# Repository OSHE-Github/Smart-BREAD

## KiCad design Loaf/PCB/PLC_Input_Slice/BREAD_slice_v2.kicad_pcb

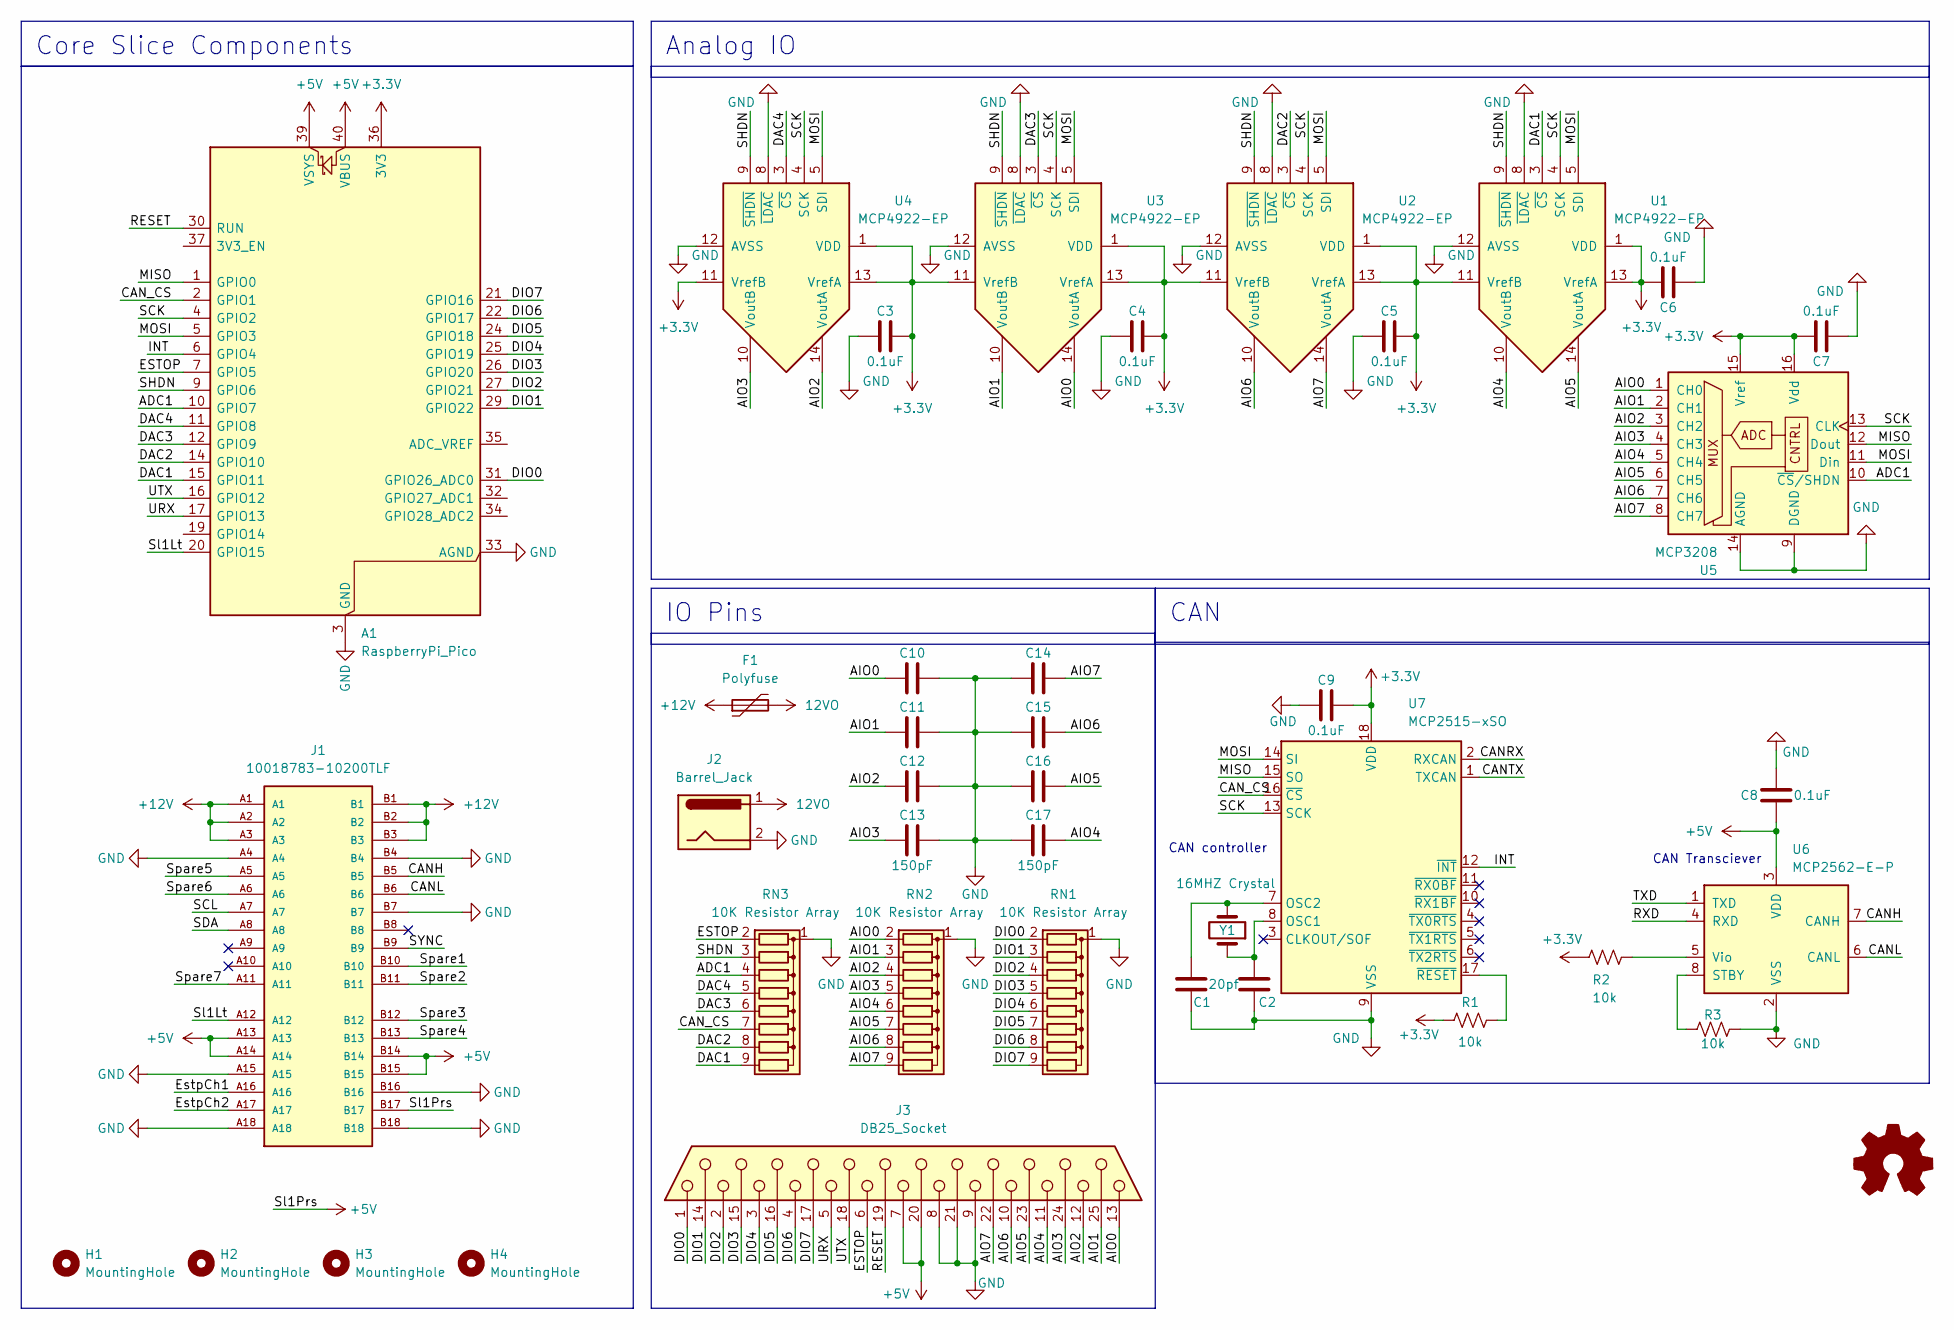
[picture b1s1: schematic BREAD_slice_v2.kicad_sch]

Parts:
A1: RaspberryPi_Pico; RaspberryPi_Pico_Common_Unspecified
C1, C2: 20pf; C_1206_3216Metric_Pad1.33x1.80mm_HandSolder
C3, C4, C5, C6, C7, C8, C9: 0.1uF; C_1206_3216Metric_Pad1.33x1.80mm_HandSolder
C10, C11, C12, C13, C14, C15, C16, C17: 150pF; C_1206_3216Metric_Pad1.33x1.80mm_HandSolder
F1: Polyfuse; Fuse_2920_7451Metric_Pad2.10x5.45mm_HandSolder
H1, H2, H3, H4: MountingHole; MountingHole_3.2mm_M3_DIN965_Pad
J1: 10018783-10200TLF; BUS_PCIexpress_x1; PARTREV Z
J2: Barrel_Jack; BarrelJack_CUI_PJ-063AH_Horizontal
J3: DB25_Socket; DSUB-25_Socket_Horizontal_P2.77x2.84mm_EdgePinOffset4.94mm_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
Logo1: Logo_Open_Hardware_Small; OSHW-Symbol_6.7x6mm_SilkScreen
R1, R2, R3: 10k; R_1206_3216Metric_Pad1.30x1.75mm_HandSolder
RN1, RN2, RN3: 10K Resistor Array; R_Array_SIP9
U1, U2, U3, U4: MCP4922-EP; DIP-14_W7.62mm
U5: MCP3208; DIP-16_W7.62mm_LongPads
U6: MCP2562-E-P; DIP-8_W7.62mm
U7: MCP2515-xSO; DIP-18_W7.62mm
Y1: 16MHZ Crystal; Crystal_HC49-4H_Vertical

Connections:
12VO: F1.2, J2.1
+3.3V: A1.36 (3V3), C3.2, C4.2, C5.2, C6.2, C7.2, C9.2, R1.2, R2.1, U1.1 (VDD), U1.11 (VrefB), U1.13 (VrefA), U2.1 (VDD), U2.11 (VrefB), U2.13 (VrefA), U3.1 (VDD), U3.11 (VrefB), U3.13 (VrefA), U4.1 (VDD), U4.11 (VrefB), U4.13 (VrefA), U5.15 (Vref), U5.16 (Vdd), U7.18 (VDD)
+5V: A1.39 (VSYS), A1.40 (VBUS), C8.2, J1.A13, J1.A14, J1.B14, J1.B15, J1.B17, J3.7, J3.20, U6.3 (VDD)
+12V: F1.1, J1.A1, J1.A2, J1.A3, J1.B1, J1.B2, J1.B3
/ADC1: A1.10 (GPIO7), RN3.4 (R3), U5.10 (~CS/SHDN)
/AIO0: C10.1, J3.13, RN2.2 (R1), U3.14 (VoutA), U5.1 (CH0)
/AIO1: C11.1, J3.25, RN2.3 (R2), U3.10 (VoutB), U5.2 (CH1)
/AIO2: C12.1, J3.12, RN2.4 (R3), U4.14 (VoutA), U5.3 (CH2)
/AIO3: C13.1, J3.24, RN2.5 (R4), U4.10 (VoutB), U5.4 (CH3)
/AIO4: C17.2, J3.11, RN2.6 (R5), U1.10 (VoutB), U5.5 (CH4)
/AIO5: C16.2, J3.23, RN2.7 (R6), U1.14 (VoutA), U5.6 (CH5)
/AIO6: C15.2, J3.10, RN2.8 (R7), U2.10 (VoutB), U5.7 (CH6)
/AIO7: C14.2, J3.22, RN2.9 (R8), U2.14 (VoutA), U5.8 (CH7)
/CANH: J1.B5, U6.7 (CANH)
/CANL: J1.B6, U6.6 (CANL)
/CANRX: U7.2 (RXCAN)
/CANTX: U7.1 (TXCAN)
/CAN_CS: A1.2 (GPIO1), RN3.7 (R6), U7.16 (~CS)
/DAC1: A1.15 (GPIO11), RN3.9 (R8), U1.3 (~CS)
/DAC2: A1.14 (GPIO10), RN3.8 (R7), U2.3 (~CS)
/DAC3: A1.12 (GPIO9), RN3.6 (R5), U3.3 (~CS)
/DAC4: A1.11 (GPIO8), RN3.5 (R4), U4.3 (~CS)
/DIO0: A1.31 (GPIO26_ADC0), J3.1, RN1.2 (R1)
/DIO1: A1.29 (GPIO22), J3.14, RN1.3 (R2)
/DIO2: A1.27 (GPIO21), J3.2, RN1.4 (R3)
/DIO3: A1.26 (GPIO20), J3.15, RN1.5 (R4)
/DIO4: A1.25 (GPIO19), J3.3, RN1.6 (R5)
/DIO5: A1.24 (GPIO18), J3.16, RN1.7 (R6)
/DIO6: A1.22 (GPIO17), J3.4, RN1.8 (R7)
/DIO7: A1.21 (GPIO16), J3.17, RN1.9 (R8)
/ESTOP: A1.7 (GPIO5), J3.6, RN3.2 (R1)
/EstpCh1: J1.A16
/EstpCh2: J1.A17
/INT: A1.6 (GPIO4), U7.12 (~INT)
/MISO: A1.1 (GPIO0), U5.12 (Dout), U7.15 (SO)
/MOSI: A1.5 (GPIO3), U1.5 (SDI), U2.5 (SDI), U3.5 (SDI), U4.5 (SDI), U5.11 (Din), U7.14 (SI)
/RESET: A1.30 (RUN), J3.19
/RXD: U6.4 (RXD)
/SCK: A1.4 (GPIO2), U1.4 (SCK), U2.4 (SCK), U3.4 (SCK), U4.4 (SCK), U5.13 (CLK), U7.13 (SCK)
/SCL: J1.A7
/SDA: J1.A8
/SHDN: A1.9 (GPIO6), RN3.3 (R2), U1.9 (~SHDN), U2.9 (~SHDN), U3.9 (~SHDN), U4.9 (~SHDN)
/SYNC: J1.B9
/Sl1Lt: A1.20 (GPIO15), J1.A12
/Spare1: J1.B10
/Spare2: J1.B11
/Spare3: J1.B12
/Spare4: J1.B13
/Spare5: J1.A5
/Spare6: J1.A6
/Spare7: J1.A11
/TXD: U6.1 (TXD)
/URX: A1.17 (GPIO13), J3.5
/UTX: A1.16 (GPIO12), J3.18
GND: A1.3 (GND), A1.8 (GND), A1.13 (GND), A1.18 (GND), A1.23 (GND), A1.28 (GND), A1.33 (AGND), A1.38 (GND), C1.2, C2.2, C3.1, C4.1, C5.1, C6.1, C7.1, C8.1, C9.1, C10.2, C11.2, C12.2, C13.2, C14.1, C15.1, C16.1, C17.1, J1.A4, J1.A15, J1.A18, J1.B4, J1.B7, J1.B16, J1.B18, J2.2, J3.8, J3.9, J3.21, R3.1, RN1.1 (common), RN2.1 (common), RN3.1 (common), U1.8 (~LDAC), U1.12 (AVSS), U2.8 (~LDAC), U2.12 (AVSS), U3.8 (~LDAC), U3.12 (AVSS), U4.8 (~LDAC), U4.12 (AVSS), U5.9 (DGND), U5.14 (AGND), U6.2 (VSS), U7.9 (VSS)
unnamed: R3.2, U6.8 (STBY)
unnamed: R2.2, U6.5 (Vio)
unnamed: C2.1, U7.8 (OSC1), Y1.1
unnamed: C1.1, U7.7 (OSC2), Y1.2
unnamed: R1.1, U7.17 (~RESET)

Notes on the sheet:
CAN Transciever
CAN controller
CAN
IO Pins
Analog IO
Core Slice Components

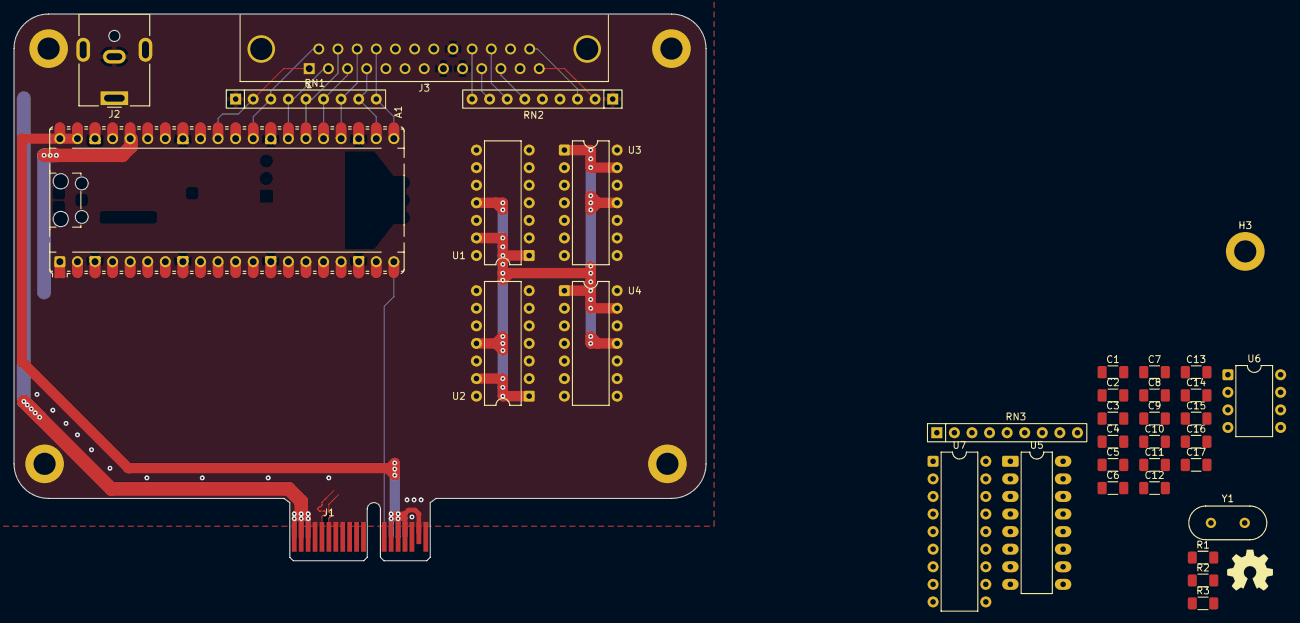
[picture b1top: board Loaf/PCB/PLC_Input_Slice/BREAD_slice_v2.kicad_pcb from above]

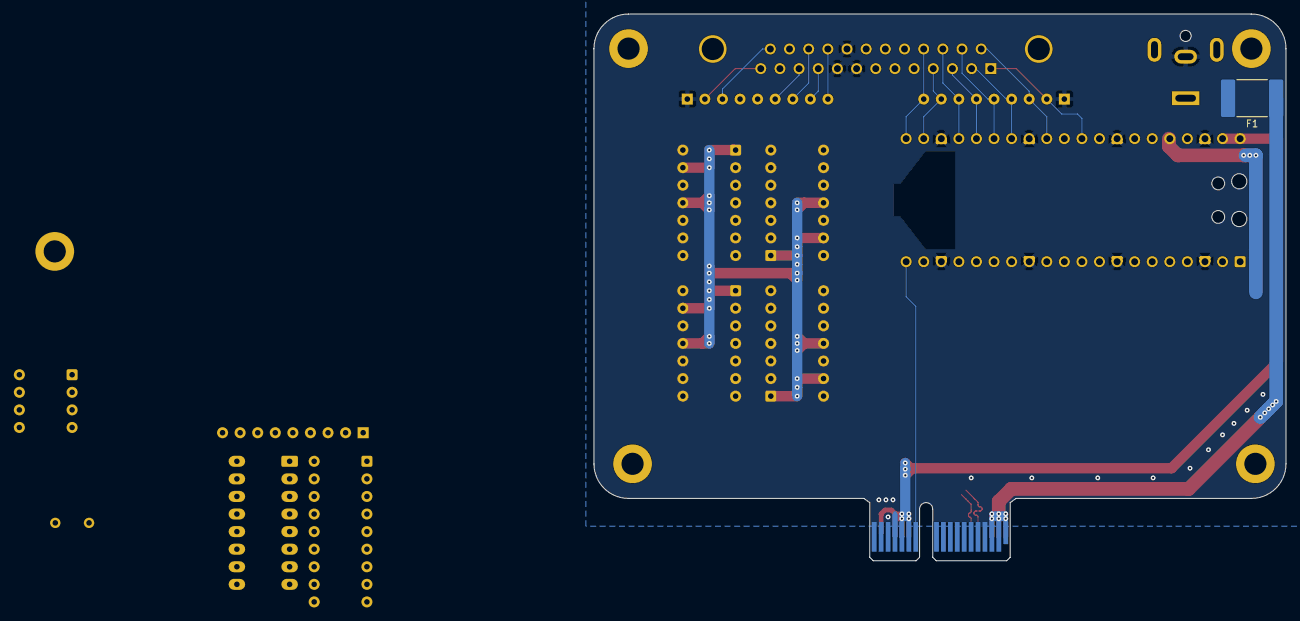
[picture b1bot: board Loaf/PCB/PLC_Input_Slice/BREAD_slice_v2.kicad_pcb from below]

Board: 2 copper layers, 100.0 x 79.0 mm, 42 parts (5 on the bottom side), 44 nets.

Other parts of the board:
H1#2: MountingHole; MountingHole_3.2mm_M3_DIN965_Pad

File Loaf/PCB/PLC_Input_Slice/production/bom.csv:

Designator,Footprint,Quantity,Value,LCSC Part #
A1,RaspberryPi_Pico_Common_Unspecified,1,RaspberryPi_Pico,
"C1, C2",1206,2,20pf,
"C10, C11, C12, C13, C14, C15, C16, C17",1206,8,150pF,
"C3, C4, C5, C6, C7, C8, C9",1206,7,0.1uF,
F1,2920,1,Polyfuse,
J1,BUS_PCIexpress_x1,1,10018783-10200TLF,
J2,BarrelJack_CUI_PJ-063AH_Horizontal,1,Barrel_Jack,
J3,DSUB-25_Socket_Horizontal_P2.77x2.84mm_EdgePinOffset4.94mm_Housed_MountingHolesOffset4.94mm,1,DB25_Socket,
LOGO1,OSHW-Symbol_6.7x6mm_SilkScreen,1,Logo_Open_Hardware_Small,
"R1, R2",1206,2,10k,
"RN1, RN2, RN3",R_Array_SIP9,3,10K Resistor Array,
"U1, U2, U3, U4",DIP-14_W7.62mm,4,MCP4922-EP,
U5,DIP-16_W7.62mm_LongPads,1,MCP3208,
U6,DIP-8_W7.62mm,1,MCP2561-E-P,
U7,DIP-18_W7.62mm,1,MCP2515-xSO,
Y1,Crystal_HC49-4H_Vertical,1,16MHZ Crystal,

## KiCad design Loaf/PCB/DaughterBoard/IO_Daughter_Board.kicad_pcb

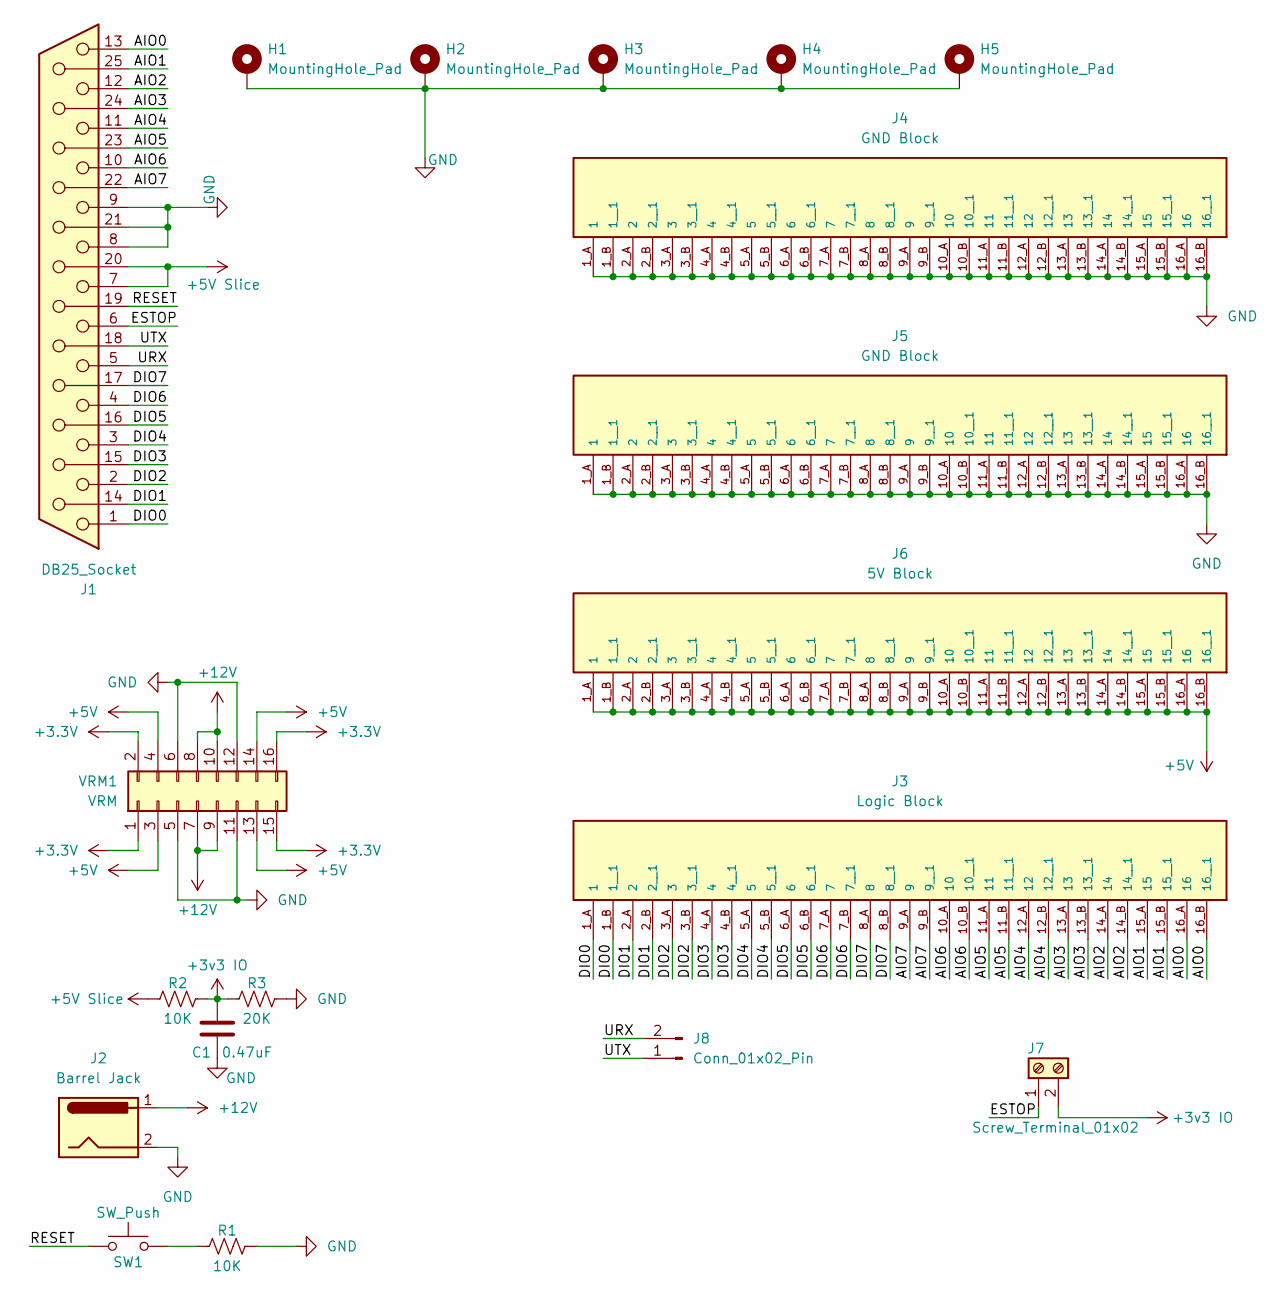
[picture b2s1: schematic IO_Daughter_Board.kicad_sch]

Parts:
C1: 0.47uF; C_1206_3216Metric_Pad1.33x1.80mm_HandSolder
H1, H2, H3, H4, H5: MountingHole_Pad; MountingHole_3.2mm_M3_DIN965_Pad
J1: DB25_Socket; DSUB-25_Socket_Horizontal_P2.77x2.84mm_EdgePinOffset4.94mm_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
J2: Barrel Jack; BarrelJack_CUI_PJ-063AH_Horizontal
J3: Logic Block; CUI_TBL009-254-16GY-2GY
J4, J5: GND Block; CUI_TBL009-254-16GY-2GY
J6: 5V Block; CUI_TBL009-254-16GY-2GY
J7: Screw_Terminal_01x02; TerminalBlock_MaiXu_MX126-5.0-02P_1x02_P5.00mm
J8: Conn_01x02_Pin; PinHeader_1x02_P2.54mm_Horizontal
R1, R2: 10K; R_1206_3216Metric_Pad1.30x1.75mm_HandSolder
R3: 20K; R_1206_3216Metric_Pad1.30x1.75mm_HandSolder
SW1: SW_Push; SW_Tactile_Straight_KSL0Axx1LFTR
VRM1: VRM; PinSocket_2x08_P2.54mm_Vertical

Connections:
+3.3V: VRM1.1, VRM1.2, VRM1.15, VRM1.16
+3v3 IO: C1.2, J7.2, R2.2, R3.1
+5V: J6.1_A (1), J6.1_B (1__1), J6.2_A (2), J6.2_B (2__1), J6.3_A (3), J6.3_B (3__1), J6.4_A (4), J6.4_B (4__1), J6.5_A (5), J6.5_B (5__1), J6.6_A (6), J6.6_B (6__1), J6.7_A (7), J6.7_B (7__1), J6.8_A (8), J6.8_B (8__1), J6.9_A (9), J6.9_B (9__1), J6.10_A (10), J6.10_B (10__1), J6.11_A (11), J6.11_B (11__1), J6.12_A (12), J6.12_B (12__1), J6.13_A (13), J6.13_B (13__1), J6.14_A (14), J6.14_B (14__1), J6.15_A (15), J6.15_B (15__1), J6.16_A (16), J6.16_B (16__1), VRM1.3, VRM1.4, VRM1.13, VRM1.14
+5V Slice: J1.7, J1.20, R2.1
+12V: J2.1, VRM1.7, VRM1.8, VRM1.9, VRM1.10
/AIO0: J1.13, J3.16_A (16), J3.16_B (16__1)
/AIO1: J1.25, J3.15_A (15), J3.15_B (15__1)
/AIO2: J1.12, J3.14_A (14), J3.14_B (14__1)
/AIO3: J1.24, J3.13_A (13), J3.13_B (13__1)
/AIO4: J1.11, J3.12_A (12), J3.12_B (12__1)
/AIO5: J1.23, J3.11_A (11), J3.11_B (11__1)
/AIO6: J1.10, J3.10_A (10), J3.10_B (10__1)
/AIO7: J1.22, J3.9_A (9), J3.9_B (9__1)
/DIO0: J1.1, J3.1_A (1), J3.1_B (1__1)
/DIO1: J1.14, J3.2_A (2), J3.2_B (2__1)
/DIO2: J1.2, J3.3_A (3), J3.3_B (3__1)
/DIO3: J1.15, J3.4_A (4), J3.4_B (4__1)
/DIO4: J1.3, J3.5_A (5), J3.5_B (5__1)
/DIO5: J1.16, J3.6_A (6), J3.6_B (6__1)
/DIO6: J1.4, J3.7_A (7), J3.7_B (7__1)
/DIO7: J1.17, J3.8_A (8), J3.8_B (8__1)
/ESTOP: J1.6, J7.1
/RESET: J1.19, SW1.1
/URX: J1.5, J8.2
/UTX: J1.18, J8.1
GND: C1.1, H1.1 (1_1), H2.1 (1_1), H3.1 (1_1), H4.1 (1_1), H5.1 (1_1), J1.8, J1.9, J1.21, J2.2, J4.1_A (1), J4.1_B (1__1), J4.2_A (2), J4.2_B (2__1), J4.3_A (3), J4.3_B (3__1), J4.4_A (4), J4.4_B (4__1), J4.5_A (5), J4.5_B (5__1), J4.6_A (6), J4.6_B (6__1), J4.7_A (7), J4.7_B (7__1), J4.8_A (8), J4.8_B (8__1), J4.9_A (9), J4.9_B (9__1), J4.10_A (10), J4.10_B (10__1), J4.11_A (11), J4.11_B (11__1), J4.12_A (12), J4.12_B (12__1), J4.13_A (13), J4.13_B (13__1), J4.14_A (14), J4.14_B (14__1), J4.15_A (15), J4.15_B (15__1), J4.16_A (16), J4.16_B (16__1), J5.1_A (1), J5.1_B (1__1), J5.2_A (2), J5.2_B (2__1), J5.3_A (3), J5.3_B (3__1), J5.4_A (4), J5.4_B (4__1), J5.5_A (5), J5.5_B (5__1), J5.6_A (6), J5.6_B (6__1), J5.7_A (7), J5.7_B (7__1), J5.8_A (8), J5.8_B (8__1), J5.9_A (9), J5.9_B (9__1), J5.10_A (10), J5.10_B (10__1), J5.11_A (11), J5.11_B (11__1), J5.12_A (12), J5.12_B (12__1), J5.13_A (13), J5.13_B (13__1), J5.14_A (14), J5.14_B (14__1), J5.15_A (15), J5.15_B (15__1), J5.16_A (16), J5.16_B (16__1), R1.2, R3.2, VRM1.5, VRM1.6, VRM1.11, VRM1.12
unnamed: R1.1, SW1.2

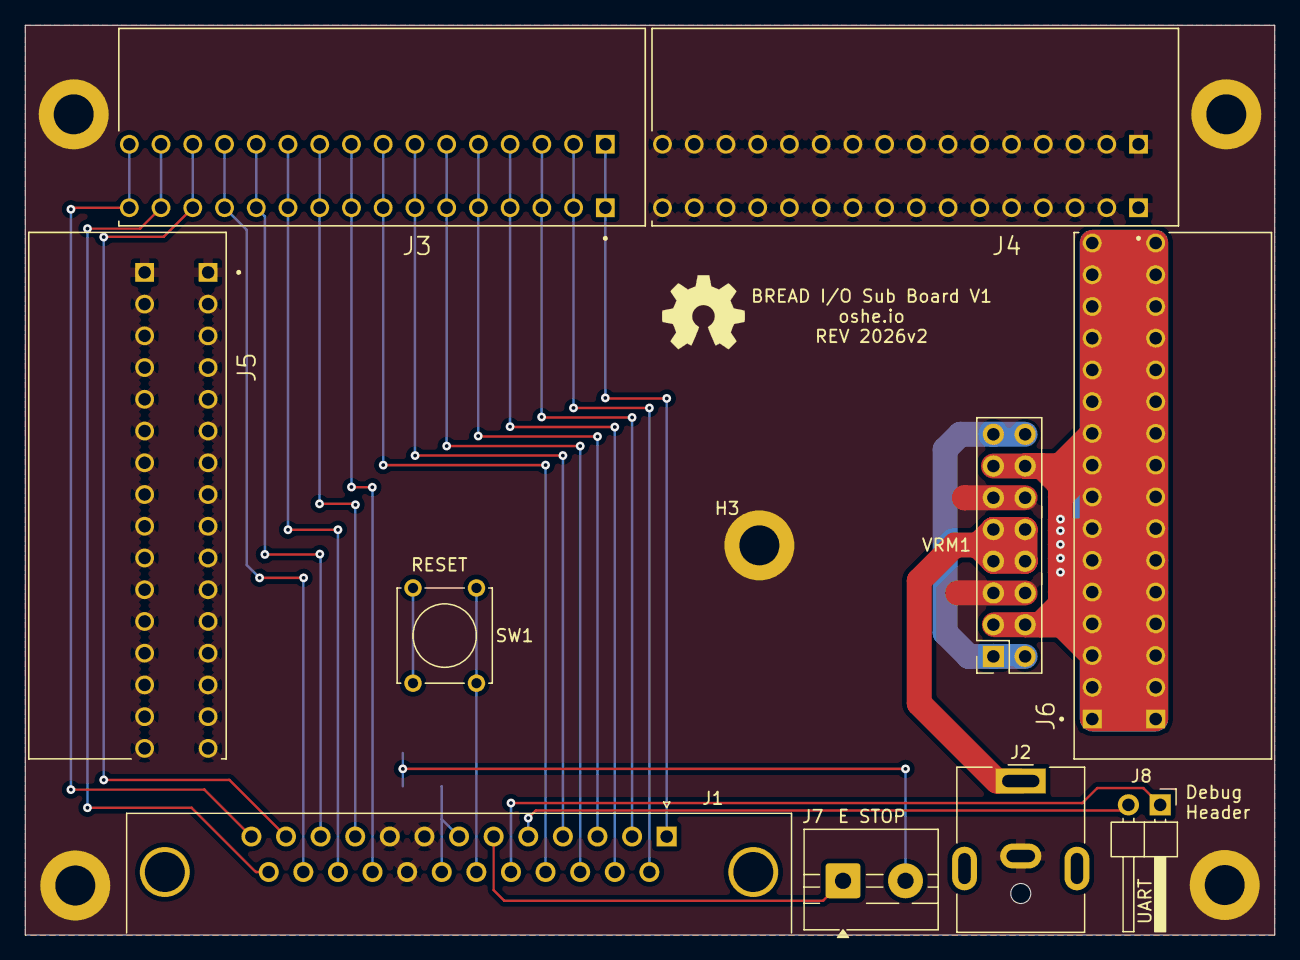
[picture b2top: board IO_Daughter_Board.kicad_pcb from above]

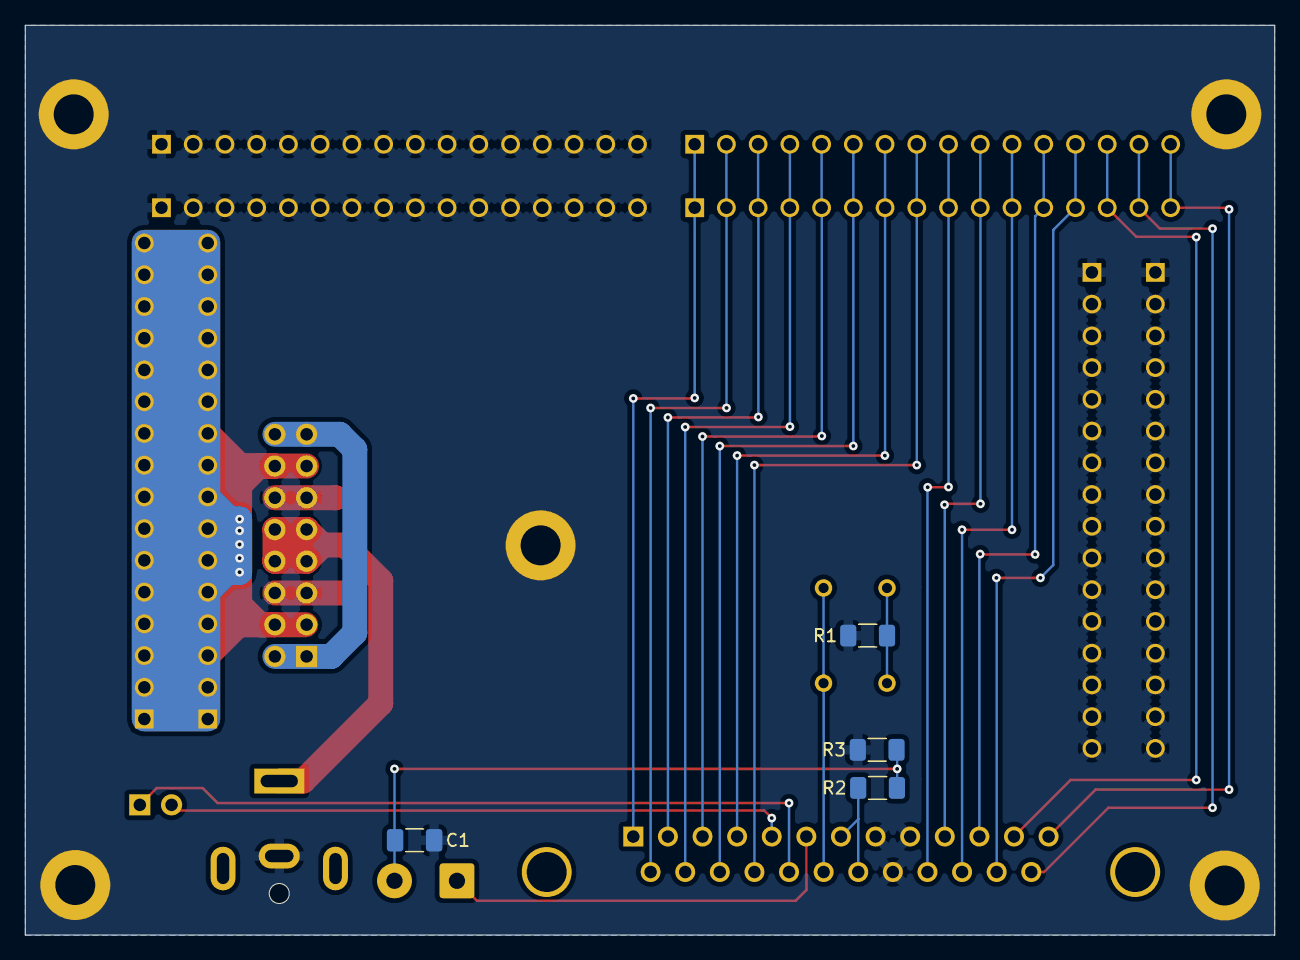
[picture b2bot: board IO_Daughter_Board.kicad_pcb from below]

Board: 2 copper layers, 100.0 x 72.8 mm, 20 parts (4 on the bottom side), 27 nets.

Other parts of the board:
Logo1: Logo_Open_Hardware_Small; OSHW-Symbol_6.7x6mm_SilkScreen

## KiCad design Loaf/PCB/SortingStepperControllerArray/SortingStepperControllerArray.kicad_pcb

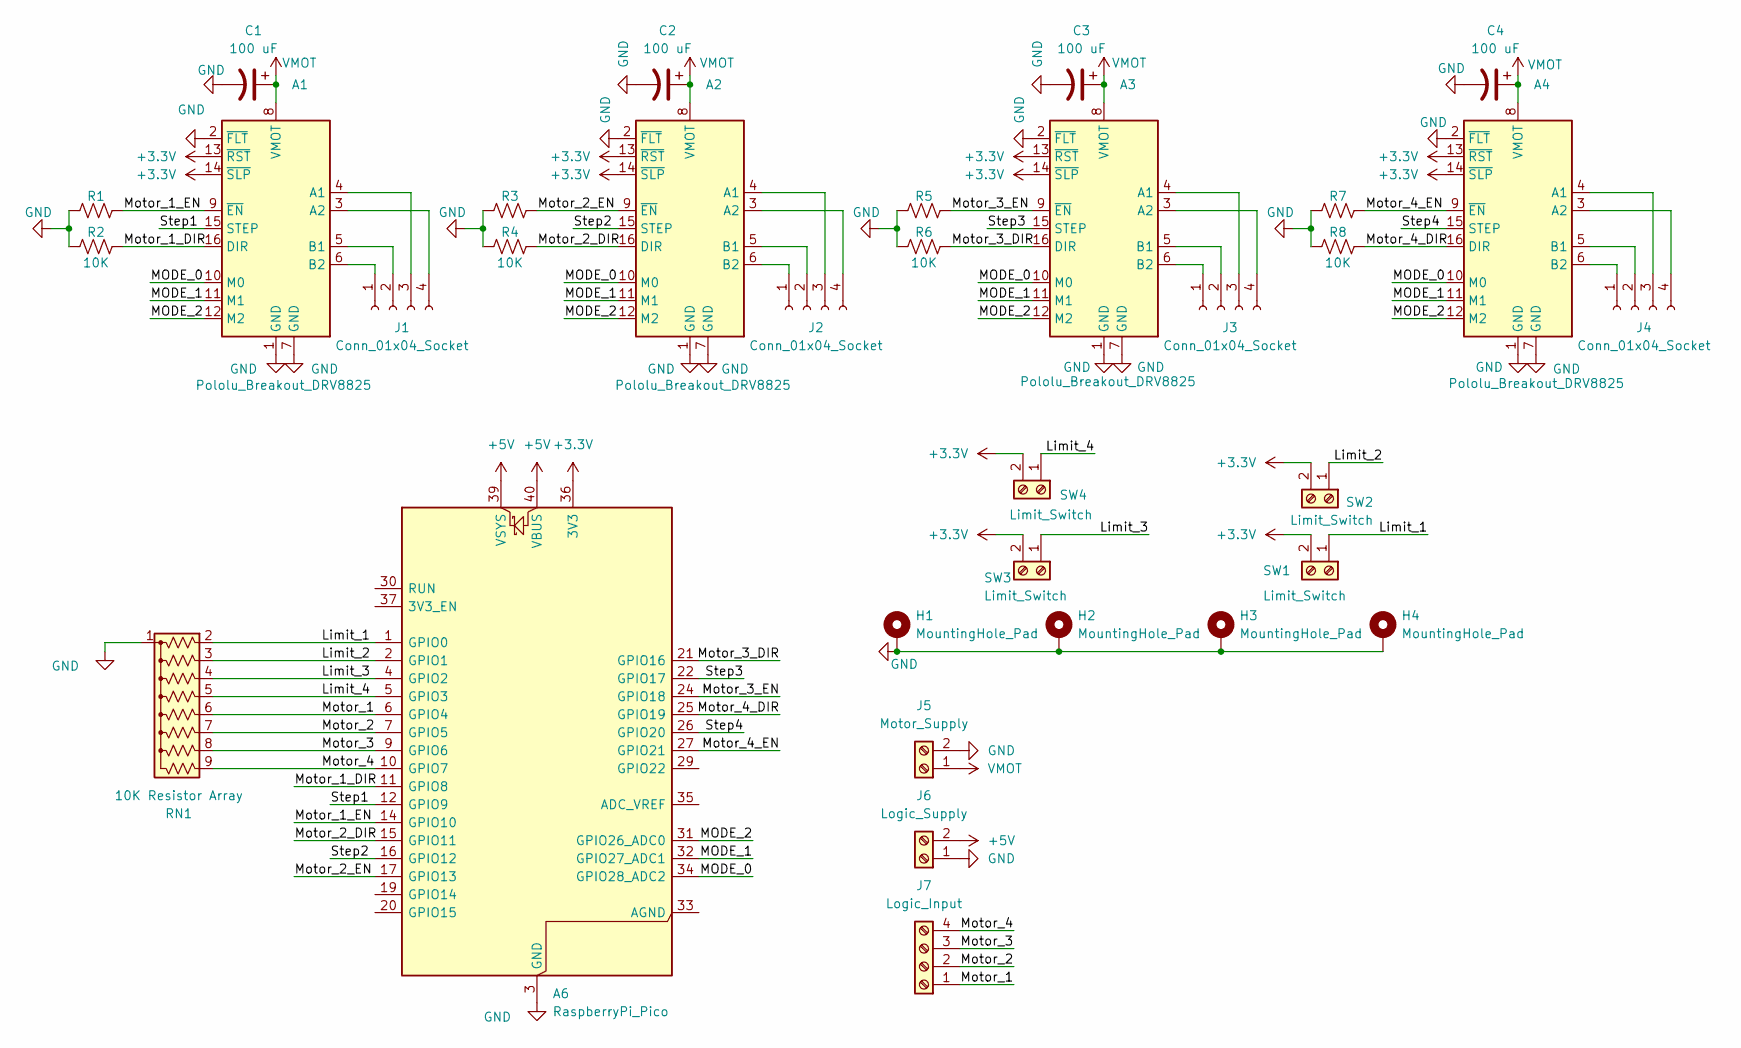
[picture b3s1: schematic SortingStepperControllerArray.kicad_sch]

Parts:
A1, A2, A3, A4: Pololu_Breakout_DRV8825; Pololu_Breakout-16_15.2x20.3mm
A6: RaspberryPi_Pico; RaspberryPi_Pico_Common_Unspecified
C1, C2, C3, C4: 100 uF; CP_Radial_D8.0mm_P3.50mm
H1, H2, H3, H4: MountingHole_Pad; MountingHole_3.2mm_M3_DIN965_Pad
J1, J2, J3, J4: Conn_01x04_Socket; JST_XH_B4B-XH-A_1x04_P2.50mm_Vertical
J5: Motor_Supply; TerminalBlock_TE_282834-2_1x02_P2.54mm_Horizontal
J6: Logic_Supply; TerminalBlock_TE_282834-2_1x02_P2.54mm_Horizontal
J7: Logic_Input; TerminalBlock_TE_282834-4_1x04_P2.54mm_Horizontal
R1, R2, R3, R4, R5, R6, R7, R8: 10K; R_1206_3216Metric_Pad1.30x1.75mm_HandSolder
RN1: 10K Resistor Array; R_Array_SIP9
SW1, SW2, SW3, SW4: Limit_Switch; TerminalBlock_TE_282834-2_1x02_P2.54mm_Horizontal

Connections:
+3.3V: A1.13 (~RST), A1.14 (~SLP), A2.13 (~RST), A2.14 (~SLP), A3.13 (~RST), A3.14 (~SLP), A4.13 (~RST), A4.14 (~SLP), A6.36 (3V3), SW1.2, SW2.2, SW3.2, SW4.2
+5V: A6.39 (VSYS), A6.40 (VBUS), J6.2
/Limit_1: A6.1 (GPIO0), RN1.2 (R1), SW1.1
/Limit_2: A6.2 (GPIO1), RN1.3 (R2), SW2.1
/Limit_3: A6.4 (GPIO2), RN1.4 (R3), SW3.1
/Limit_4: A6.5 (GPIO3), RN1.5 (R4), SW4.1
/MODE_0: A1.10 (M0), A2.10 (M0), A3.10 (M0), A4.10 (M0), A6.34 (GPIO28_ADC2)
/MODE_1: A1.11 (M1), A2.11 (M1), A3.11 (M1), A4.11 (M1), A6.32 (GPIO27_ADC1)
/MODE_2: A1.12 (M2), A2.12 (M2), A3.12 (M2), A4.12 (M2), A6.31 (GPIO26_ADC0)
/Motor_1: A6.6 (GPIO4), J7.1, RN1.6 (R5)
/Motor_1_DIR: A1.16 (DIR), A6.11 (GPIO8), R2.2
/Motor_1_EN: A1.9 (~EN), A6.14 (GPIO10), R1.2
/Motor_2: A6.7 (GPIO5), J7.2, RN1.7 (R6)
/Motor_2_DIR: A2.16 (DIR), A6.15 (GPIO11), R4.2
/Motor_2_EN: A2.9 (~EN), A6.17 (GPIO13), R3.2
/Motor_3: A6.9 (GPIO6), J7.3, RN1.8 (R7)
/Motor_3_DIR: A3.16 (DIR), A6.21 (GPIO16), R6.2
/Motor_3_EN: A3.9 (~EN), A6.24 (GPIO18), R5.2
/Motor_4: A6.10 (GPIO7), J7.4, RN1.9 (R8)
/Motor_4_DIR: A4.16 (DIR), A6.25 (GPIO19), R8.2
/Motor_4_EN: A4.9 (~EN), A6.27 (GPIO21), R7.2
/Step1: A1.15 (STEP), A6.12 (GPIO9)
/Step2: A2.15 (STEP), A6.16 (GPIO12)
/Step3: A3.15 (STEP), A6.22 (GPIO17)
/Step4: A4.15 (STEP), A6.26 (GPIO20)
GND: A1.1 (GND), A1.2 (~FLT), A1.7 (GND), A2.1 (GND), A2.2 (~FLT), A2.7 (GND), A3.1 (GND), A3.2 (~FLT), A3.7 (GND), A4.1 (GND), A4.2 (~FLT), A4.7 (GND), A6.3 (GND), A6.8 (GND), A6.13 (GND), A6.18 (GND), A6.23 (GND), A6.28 (GND), A6.38 (GND), C1.2, C2.2, C3.2, C4.2, H1.1 (1_1), H2.1 (1_1), H3.1 (1_1), H4.1 (1_1), J5.2, J6.1, R1.1, R2.1, R3.1, R4.1, R5.1, R6.1, R7.1, R8.1, RN1.1 (common)
unnamed: A1.4 (A1), J1.3
unnamed: A1.3 (A2), J1.4
unnamed: A1.5 (B1), J1.2
unnamed: A1.6 (B2), J1.1
unnamed: A2.4 (A1), J2.3
unnamed: A2.3 (A2), J2.4
unnamed: A2.5 (B1), J2.2
unnamed: A2.6 (B2), J2.1
unnamed: A3.4 (A1), J3.3
unnamed: A3.3 (A2), J3.4
unnamed: A3.5 (B1), J3.2
unnamed: A3.6 (B2), J3.1
unnamed: A4.4 (A1), J4.3
unnamed: A4.3 (A2), J4.4
unnamed: A4.5 (B1), J4.2
unnamed: A4.6 (B2), J4.1
VMOT: A1.8 (VMOT), A2.8 (VMOT), A3.8 (VMOT), A4.8 (VMOT), C1.1, C2.1, C3.1, C4.1, J5.1

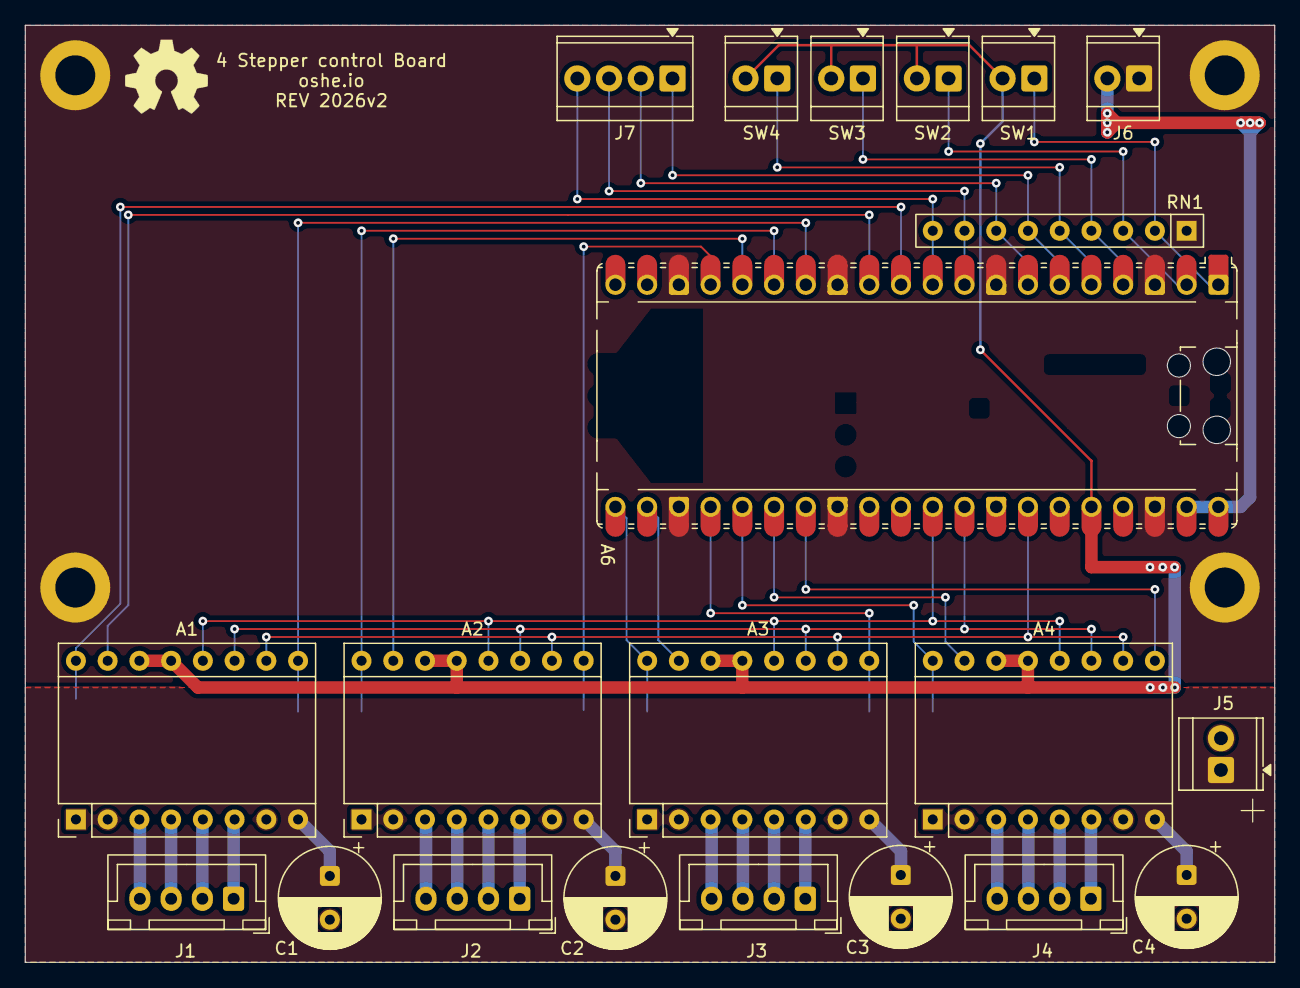
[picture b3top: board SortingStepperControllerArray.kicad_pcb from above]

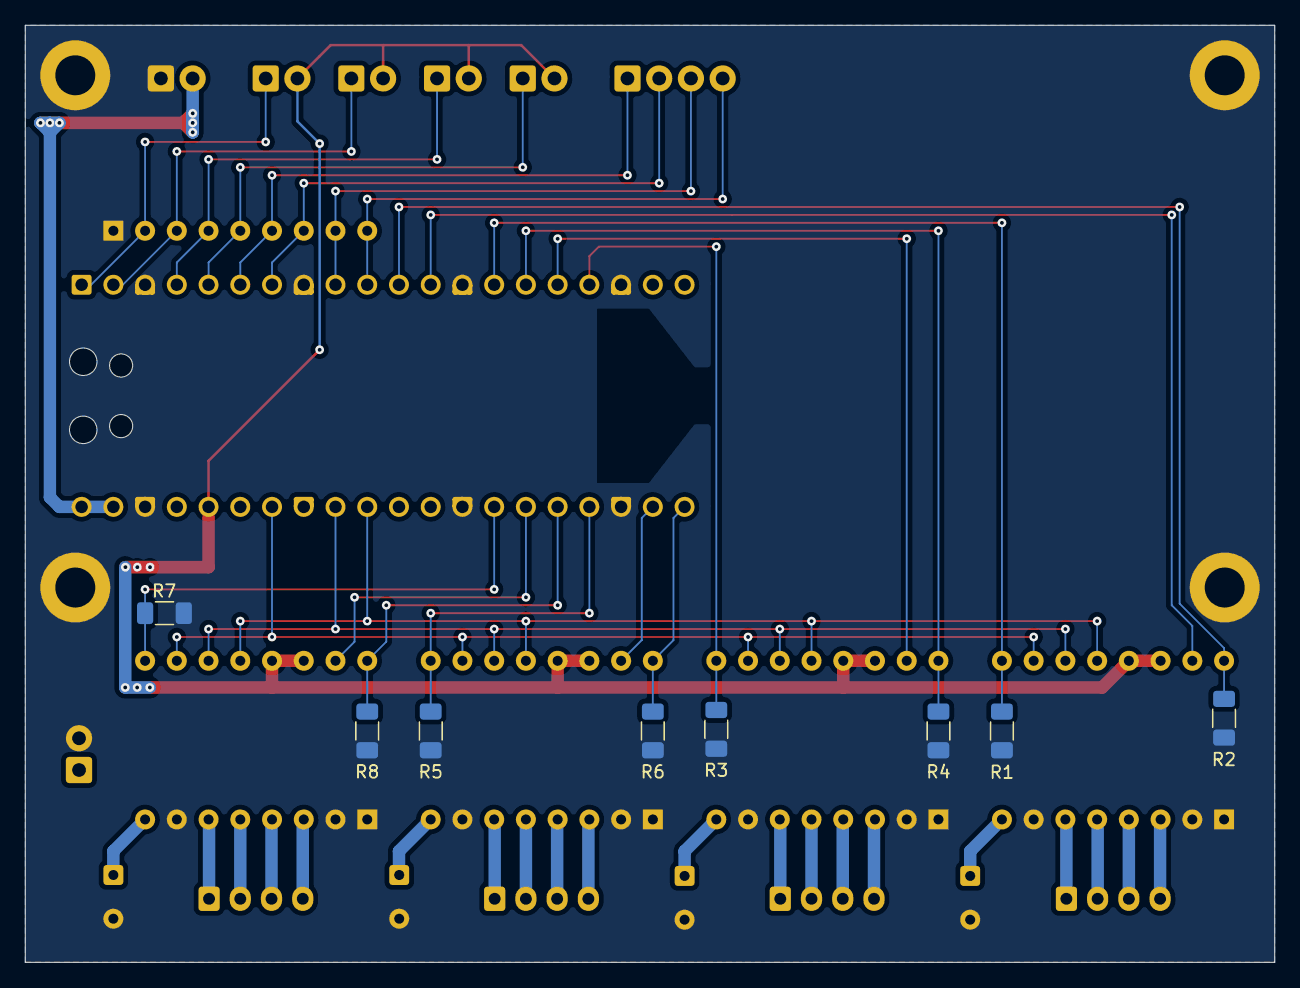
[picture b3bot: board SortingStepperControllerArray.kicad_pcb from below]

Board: 2 copper layers, 100.0 x 75.0 mm, 34 parts (8 on the bottom side), 43 nets.

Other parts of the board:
Logo1: Logo_Open_Hardware_Small; OSHW-Symbol_6.7x6mm_SilkScreen

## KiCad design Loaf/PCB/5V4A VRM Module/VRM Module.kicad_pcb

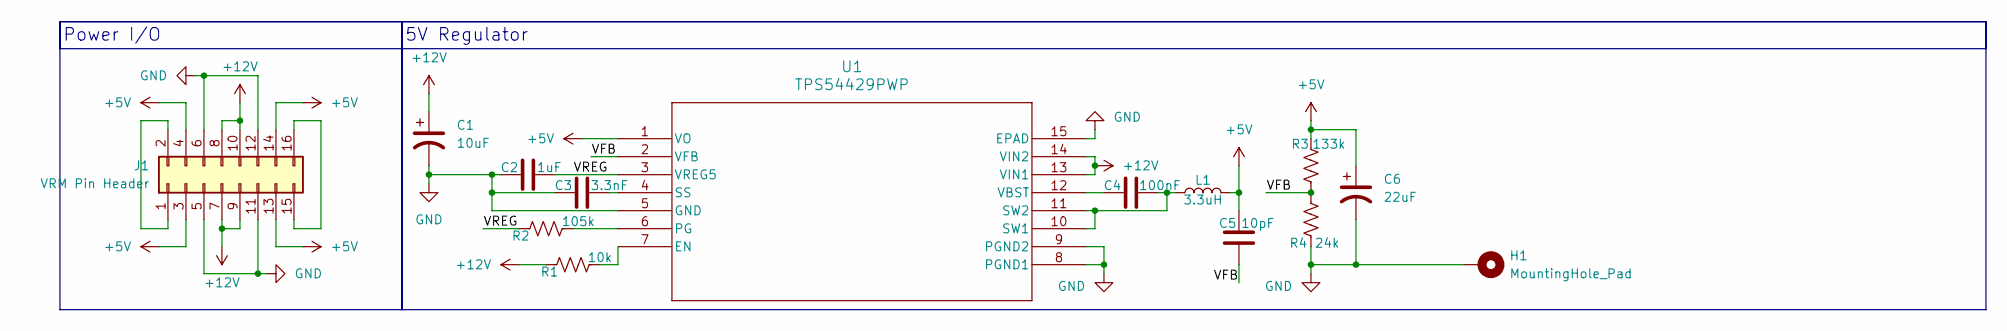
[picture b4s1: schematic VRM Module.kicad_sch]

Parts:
C1: 10uF; CP_Radial_D5.0mm_P2.50mm
C2: 1uF; C_1206_3216Metric_Pad1.33x1.80mm_HandSolder
C3: 3.3nF; C_1206_3216Metric_Pad1.33x1.80mm_HandSolder
C4: 100nF; C_1206_3216Metric_Pad1.33x1.80mm_HandSolder
C5: 10pF; C_1206_3216Metric_Pad1.33x1.80mm_HandSolder
C6: 22uF; CP_Radial_D5.0mm_P2.50mm
H1: MountingHole_Pad; MountingHole_3.2mm_M3_DIN965_Pad
J1: VRM Pin Header; PinHeader_2x08_P2.54mm_Vertical
L1: 3.3uH; R_1206_3216Metric_Pad1.30x1.75mm_HandSolder
R1: 10k; R_1206_3216Metric_Pad1.30x1.75mm_HandSolder
R2: 105k; R_1206_3216Metric_Pad1.30x1.75mm_HandSolder
R3: 133k; R_1206_3216Metric_Pad1.30x1.75mm_HandSolder
R4: 24k; R_1206_3216Metric_Pad1.30x1.75mm_HandSolder
U1: TPS54429PWP; Texas_HTSSOP-14-1EP_4.4x5mm_P0.65mm_EP3.4x5mm_Mask2.94x3.34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

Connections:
+5V: C5.2, C6.1, J1.3, J1.4, J1.13, J1.14, L1.2, R3.2, U1.1 (VO)
+12V: C1.1, J1.7, J1.8, J1.9, J1.10, R1.1, U1.13 (VIN1), U1.14 (VIN2)
/VFB: C5.1, R3.1, R4.2, U1.2 (VFB)
/VREG: C2.2, R2.1, U1.3 (VREG5)
GND: C1.2, C2.1, C3.1, C6.2, H1.1 (1_1), J1.5, J1.6, J1.11, J1.12, R4.1, U1.5 (GND), U1.8 (PGND1), U1.9 (PGND2), U1.15 (EPAD)
unnamed: J1.1, J1.2
unnamed: J1.15, J1.16
unnamed: R1.2, U1.7 (EN)
unnamed: R2.2, U1.6 (PG)
unnamed: C3.2, U1.4 (SS)
unnamed: C4.2, L1.1, U1.10 (SW1), U1.11 (SW2)
unnamed: C4.1, U1.12 (VBST)

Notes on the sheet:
5V Regulator
Power I/O

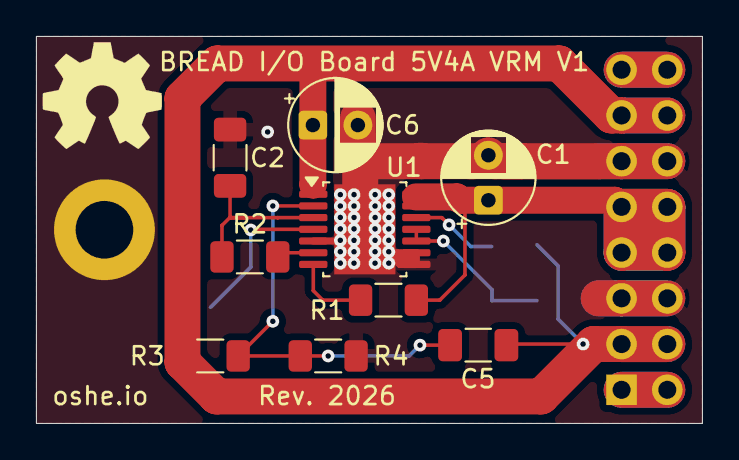
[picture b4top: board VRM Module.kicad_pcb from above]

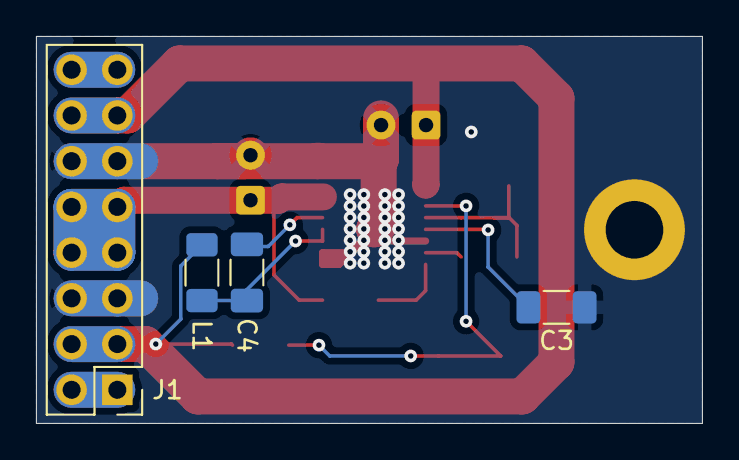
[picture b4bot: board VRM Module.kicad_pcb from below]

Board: 2 copper layers, 37.0 x 21.5 mm, 15 parts (5 on the bottom side), 12 nets.

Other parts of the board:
Logo1: Logo_Open_Hardware_Small; OSHW-Symbol_6.7x6mm_SilkScreen

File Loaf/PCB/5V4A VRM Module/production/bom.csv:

Designator,Footprint,Quantity,Value,LCSC Part #
C1,CP_Radial_D5.0mm_P2.50mm,1,10uF,
C2,1206,1,1uF,
C3,1206,1,3.3uF,
C4,1206,1,100nF,
C5,1206,1,10pF,
C6,CP_Radial_D5.0mm_P2.50mm,1,22uF,
J1,PinHeader_2x08_P2.54mm_Vertical,1,VRM Pin Header,
L1,1206,1,3.3uH,
LOGO1,OSHW-Symbol_6.7x6mm_SilkScreen,1,Logo_Open_Hardware_Small,
R1,1206,1,10k,
R2,1206,1,105k,
R3,1206,1,133k,
R4,1206,1,24k,
U1,Texas_HTSSOP-14-1EP_4.4x5mm_P0.65mm_EP3.4x5mm_Mask2.94x3.34mm,1,TPS54429PWP,
